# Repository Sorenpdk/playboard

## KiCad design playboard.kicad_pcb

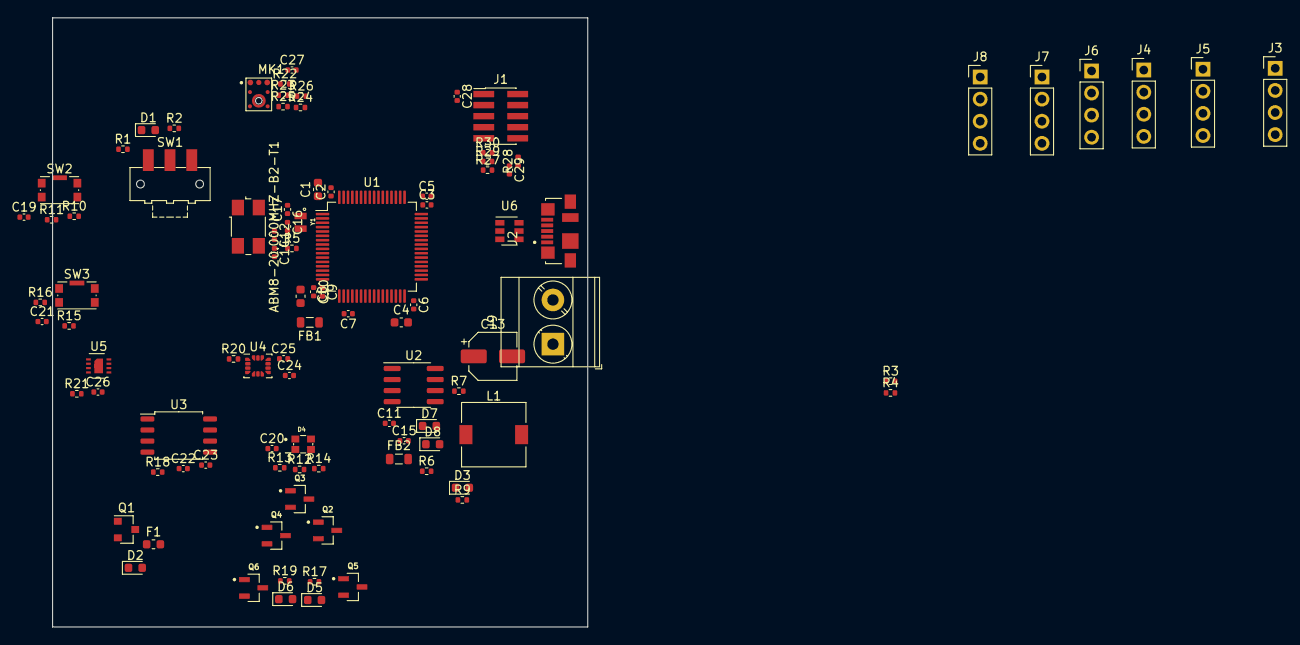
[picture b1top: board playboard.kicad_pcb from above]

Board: 2 copper layers, 61.5 x 70.0 mm, 96 parts (0 on the bottom side), 90 nets, no tracks yet.

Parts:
ABM8-20.000MHZ-B2-T1: 20MHz; Crystal_SMD_0603-4Pin_6.0x3.5mm
C1: 4u7; C_0603_1608Metric
C2, C3, C5, C6, C7, C9, C19, C21, C22, C23, C24, C25, C26, C27, C28, C29: 100n; C_0402_1005Metric
C4: 2u2; C_0603_1608Metric
C8: 1u; C_0603_1608Metric
C10: 10n; C_0402_1005Metric
C11: 47u; C_0402_1005Metric
C12, C14: 12p; C_0402_1005Metric
C13: 220u; CP_Elec_5x3
C15, C20: 10u; C_0402_1005Metric
C16, C17: 9pF; C_0402_1005Metric
D1: LED_Small; LED_0603_1608Metric
D2: B5817W-B5819W N1752; D_0603_1608Metric
D3, D5, D6: Blue; LED_0603_1608Metric
D4: ASMB-KTF0-0A306; LED_ASMB-KTF0-0A306
D7, D8: D_Schottky_Small; D_0603_1608Metric
F1: 500mA; Fuse_0603_1608Metric
FB1, FB2: 600 @ 600MHz; L_0805_2012Metric
J1: Conn_ARM_JTAG_SWD_10; PinHeader_2x05_P1.27mm_Vertical_SMD
J2: 47346-0001; MOLEX_47346-0001
J3, J4, J5, J6, J7, J8: Conn_01x04_Male; PinHeader_1x04_P2.54mm_Vertical
J9: Screw_Terminal_01x02; TerminalBlock_Phoenix_MKDS-3-2-5.08_1x02_P5.08mm_Horizontal
L1: 27u; L_7.3x7.3_H4.5
MK1: PMM-3738-VM1010-R; MIC_PMM-3738-VM1010-R
Q1: AO3401A; SOT-23
Q2, Q3, Q4, Q5, Q6: FDV305N; SOT95P240X111-3N
R1, R11, R16, R18, R20, R21, R24, R25: 10k; R_0402_1005Metric
R2, R9, R10, R15, R17, R19: 1k; R_0402_1005Metric
R3, R4: 2k2; R_0402_1005Metric
R5: 47; R_0402_1005Metric
R6: 3k; R_0402_1005Metric
R7: 1k78; R_0402_1005Metric
R12: 220; R_0402_1005Metric
R13, R14: 120; R_0402_1005Metric
R22: 0; R_0402_1005Metric
R23: 150k; R_0402_1005Metric
R26: 301k; R_0402_1005Metric
R27, R28, R29, R30: 22; R_0402_1005Metric
SW1: SW_SPDT; SW_SPDT_CK-JS102011SAQN
SW2, SW3: SW_Push; SW_Push_1P1T-SH_NO_CK_KMR2xxG
U1: STM32F411RETx; LQFP-64_10x10mm_P0.5mm
U2: MIC4684; SOIC-8_3.9x4.9mm_P1.27mm
U3: MX25R3235FM2xx1; SOP-8_5.28x5.23mm_P1.27mm
U4: LSM6DS3; LGA-14_3x2.5mm_P0.5mm_LayoutBorder3x4y
U5: SHT30-DIS; Sensirion_DFN-8-1EP_2.5x2.5mm_P0.5mm_EP1.1x1.7mm
U6: USBLC6-2SC6; SOT-23-6
Y1: ABS06-32.768KHZ-T; XTAL_ABS06-32.768KHZ-T

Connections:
+3.3VA: C8.1, C9.1, C10.1, FB1.2, U1.13
+3V3: C1.1, C2.1, C3.1, C5.1, C6.1, C7.1, C13.1, C22.1, C23.1, C24.2, C25.2, C26.2, C27.2, C28.1, D3.2, D5.2, D6.2, FB1.1, J1.1, J3.1, J5.1, J5.2, J7.1, L1.2, MK1.6, R3.2, R4.2, R6.2, R20.1, R21.1, SW1.1, U1.1, U1.19, U1.32, U1.48, U1.64, U3.8, U4.2, U4.3, U4.5, U4.8
ACC_CS!: R20.2, U1.24, U4.12
ACC_INT1: U1.27, U4.4
ACC_INT2: U1.28, U4.9
ACC_MISO_SA0: U1.22, U4.1
ACC_MOSI_SDA: U1.23, U4.14
ACC_SCLK_SCL: U1.21, U4.13
ADC1_IN1: J6.1, U1.15
BOOT0: R1.2, U1.60
BUTTON_1: C19.1, R10.1, R11.2, U1.26
BUTTON_2: C21.1, R15.1, R16.2, U1.25
DAC_OUT1: J6.4, U1.20
EXT_GPIO_PC0: J4.1, U1.8
EXT_GPIO_PC3: J3.2, U1.11
FLASH_CS!: U1.33, U3.1
FLASH_HOLD!: U1.40, U3.7
FLASH_MISO: R18.1, U1.35, U3.2
FLASH_MOSI: U1.36, U3.5
FLASH_SCLK: U1.34, U3.6
FLASH_WP!: U1.42, U3.3
GND: ABM8-20.000MHZ-B2-T1.2, ABM8-20.000MHZ-B2-T1.4, C1.2, C2.2, C3.2, C4.2, C5.2, C6.2, C7.2, C8.2, C9.2, C10.2, C11.2, C12.2, C13.2, C14.2, C16.2, C17.2, C19.2, C20.1, C21.2, C22.2, C23.2, C24.1, C25.1, C26.1, C27.1, C28.2, C29.2, D8.2, J1.3, J1.5, J1.9, J2.5, J5.3, J5.4, J6.2, J6.3, J9.1, MK1.4, MK1.8, Q1.1, Q2.3, Q3.3, Q4.3, Q5.3, Q6.3, R2.1, R7.1, R9.1, R18.2, R24.2, SW1.3, SW2.1, SW3.1, U1.12, U1.18, U1.31, U1.47, U1.63, U2.2, U2.6, U2.7, U3.4, U4.6, U4.7, U6.2
HSE_IN: ABM8-20.000MHZ-B2-T1.1, C12.1, U1.5
HSE_OUT: R5.2, U1.6
MCO_1: J8.2, U1.41
MIC_GA1: MK1.3, R22.1, R25.1
MIC_GA2: MK1.2, R23.2, R26.2
MIC_MODE: MK1.5, R24.1, U1.9
MIC_VOUT_ANALOG: MK1.1, U1.10
NRST: C29.1, R28.1, U1.7
unnamed: ABM8-20.000MHZ-B2-T1.3, C14.1, R5.1
unnamed: C4.1, U1.30
unnamed: C11.1, D7.2, FB2.2, U2.3, U2.8
unnamed: C15.1, D7.1, U2.4
unnamed: C15.2, D8.1, L1.1, U2.1
unnamed: D1.1, R2.2
unnamed: D1.2, R1.1, SW1.2
unnamed: D2.1, F1.2, Q1.2
unnamed: D3.1, R9.2
unnamed: D4.2, R12.1
unnamed: D4.3, R14.1
unnamed: D4.4, R13.1
unnamed: D5.1, R17.2
unnamed: D6.1, R19.2
unnamed: F1.1, FB2.1
unnamed: J1.2, R30.2
unnamed: J1.4, R29.2
unnamed: J1.6, R27.2
unnamed: J1.10, R28.2
unnamed: J2.S1, J2.S2, J2.S3, J2.S4, J2.S5, J2.S6
unnamed: Q2.2, R12.2
unnamed: Q3.2, R13.2
unnamed: Q4.2, R14.2
unnamed: Q5.2, R17.1
unnamed: Q6.2, R19.1
unnamed: R6.1, R7.2, U2.5
unnamed: R10.2, SW2.2
unnamed: R15.2, SW3.2
unnamed: R22.2, R23.1
unnamed: R25.2, R26.1
unnamed: U5.8, U5.9
OSC32_IN: C16.1, U1.3, Y1.1
OSC32_OUT: C17.1, U1.4, Y1.2
RGB_BLUE: Q4.1, U1.39
RGB_GREEN: Q3.1, U1.38
RGB_RED: Q2.1, U1.37
SPI3_MISO: J4.3, U1.52
SPI3_MOSI: J4.4, U1.53
SPI3_SCLK: J4.2, U1.51
SWCLK: R29.1, U1.49
SWDIO: R30.1, U1.46
SWO: R27.1, U1.55
TEMP_CS: R21.2, U1.56
TEMP_SCL: R4.1, U1.61
TEMP_SDA: R3.1, U1.59
TIM5_CH1: J3.4, U1.14
TIM11_CH1: J3.3, U1.62
USART1_RX: J8.4, U1.43
USART1_TX: J8.3, U1.58
USART2_RX: J7.3, U1.17
USART2_TX: J7.2, U1.16
USB_CONN_D+: J2.3, U6.1
USB_CONN_D-: J2.2, U6.3
USB_D+: U1.45, U6.6
USB_D-: U1.44, U6.4
USER_LD1: Q5.1, U1.29
USER_LD2: Q6.1, U1.50
VBUS: D2.2, J2.1, U6.5
VCC: C20.2, D4.1, J9.2, Q1.3, R11.1, R16.1
WOS_TRIGGER: MK1.7, U1.2

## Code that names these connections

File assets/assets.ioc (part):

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Mcu.Name=STM32F446R(C-E)Tx
Mcu.Package=LQFP64
Mcu.UserName=STM32F446RETx
PA0-WKUP.Signal=S_TIM5_CH1
PA1.Signal=ADCx_IN1
PA10.Signal=USART1_RX
PA11.Mode=Device_Only
PA11.Signal=USB_OTG_FS_DM
PA12.Mode=Device_Only
PA12.Signal=USB_OTG_FS_DP
PA13.Mode=Trace_Asynchronous_SW
PA13.Signal=SYS_JTMS-SWDIO
PA14.Mode=Trace_Asynchronous_SW
PA14.Signal=SYS_JTCK-SWCLK
PA15.GPIOParameters=GPIO_Label
PA15.GPIO_Label=USER_LED2
PA15.Signal=GPIO_Output
PA2.Mode=Asynchronous
PA2.Signal=USART2_TX
PA3.Mode=Asynchronous
PA3.Signal=USART2_RX
PA4.Signal=COMP_DAC1_group
PA5.GPIOParameters=GPIO_Label
PA5.GPIO_Label=ACC_SCLK_SCL
PA5.Mode=Full_Duplex_Master
PA5.Signal=SPI1_SCK
PA6.GPIOParameters=GPIO_Label
PA6.GPIO_Label=ACC_MISO_SA0
PA6.Mode=Full_Duplex_Master
PA6.Signal=SPI1_MISO
PA7.GPIOParameters=GPIO_Label
PA7.GPIO_Label=ACC_MOSI_SDA
PA7.Mode=Full_Duplex_Master
PA7.Signal=SPI1_MOSI
PA8.Mode=Clock-out-1
PA8.Signal=RCC_MCO_1
PA9.GPIOParameters=GPIO_Label
PA9.GPIO_Label=FLASH_WP\!
PA9.Signal=GPIO_Output
PB0.GPIOParameters=GPIO_Label
PB0.GPIO_Label=BUTTON_1
PB0.Signal=GPXTI0
PB1.GPIOParameters=GPIO_Label
PB1.GPIO_Label=ACC_INT1
PB1.Signal=GPXTI1
PB10.GPIOParameters=GPIO_Label
PB10.GPIO_Label=USER_LD1
PB10.Signal=GPIO_Output
PB12.GPIOParameters=GPIO_Label
PB12.GPIO_Label=FLASH_CS\!
PB12.Signal=GPIO_Output
PB13.GPIOParameters=GPIO_Label
PB13.GPIO_Label=FLASH_SCLK
PB13.Mode=Full_Duplex_Master
PB13.Signal=SPI2_SCK
PB14.GPIOParameters=GPIO_Label
PB14.GPIO_Label=FLASH_MISO
PB14.Mode=Full_Duplex_Master
PB14.Signal=SPI2_MISO
PB15.GPIOParameters=GPIO_Label
PB15.GPIO_Label=FLASH_MOSI
PB15.Mode=Full_Duplex_Master
PB15.Signal=SPI2_MOSI
PB2.GPIOParameters=GPIO_Label
PB2.GPIO_Label=ACC_INT2
PB2.Signal=GPXTI2
PB3.Mode=Trace_Asynchronous_SW
PB3.Signal=SYS_JTDO-SWO
PB4.GPIOParameters=GPIO_Label
PB4.GPIO_Label=TEMP_CS\!mn
PB4.Signal=GPIO_Output
PB5.GPIOParameters=GPIO_Label
PB5.GPIO_Label=TEMP_DATARDY
PB5.Signal=GPXTI5
PB6.Signal=USART1_TX
PB7.GPIOParameters=GPIO_Label
PB7.GPIO_Label=TEMP_SDA
PB7.Mode=I2C
PB7.Signal=I2C1_SDA
PB8.GPIOParameters=GPIO_Label
PB8.GPIO_Label=TEMP_SCL
PB8.Mode=I2C
PB8.Signal=I2C1_SCL
PB9.Signal=S_TIM11_CH1
PC0.GPIOParameters=GPIO_Label
PC0.GPIO_Label=EXT_GPIO_PC0
PC0.Signal=GPIO_Output
PC1.GPIOParameters=GPIO_Label
PC1.GPIO_Label=MIC_MODE
PC1.Signal=GPIO_Output
PC10.GPIOParameters=GPIO_Label
PC10.GPIO_Label=EXT_SPI_SCK
PC10.Mode=Full_Duplex_Master
PC10.Signal=SPI3_SCK
PC11.GPIOParameters=GPIO_Label
PC11.GPIO_Label=EXT_SPI_MISO
PC11.Mode=Full_Duplex_Master
PC11.Signal=SPI3_MISO
PC12.GPIOParameters=GPIO_Label
PC12.GPIO_Label=EXT_SPI_MOSI
PC12.Mode=Full_Duplex_Master
PC12.Signal=SPI3_MOSI
PC13.Mode=SYS_WakeUp1
PC13.Signal=SYS_WKUP1
PC14-OSC32_IN.Mode=LSE-External-Oscillator
PC14-OSC32_IN.Signal=RCC_OSC32_IN
PC15-OSC32_OUT.Mode=LSE-External-Oscillator
PC15-OSC32_OUT.Signal=RCC_OSC32_OUT
PC2.GPIOParameters=GPIO_Label
PC2.GPIO_Label=MIC_VOUT_ANALOG
PC2.Signal=ADCx_IN12
PC3.GPIOParameters=GPIO_Label
PC3.GPIO_Label=EXT_GPIO_PC3
PC3.Signal=GPIO_Output
PC4.GPIOParameters=GPIO_Label
PC4.GPIO_Label=ACC_CS\!
PC4.Signal=GPIO_Output
PC5.GPIOParameters=GPIO_Label
PC5.GPIO_Label=BUTTON_2
PC5.Signal=GPIO_Output
PC6.GPIOParameters=GPIO_Label
PC6.GPIO_Label=RGB_RED
PC6.Signal=S_TIM3_CH1
PC7.GPIOParameters=GPIO_Label
PC7.GPIO_Label=RGB_GREEN
PC7.Signal=S_TIM3_CH2
PC8.GPIOParameters=GPIO_Label
PC8.GPIO_Label=RGB_BLUE
PC8.Signal=S_TIM3_CH3
PC9.GPIOParameters=GPIO_Label
PC9.GPIO_Label=FLASH_HOLD\!
PC9.Signal=GPIO_Output
PD2.Signal=GPIO_Output
PH0-OSC_IN.Mode=HSE-External-Oscillator
PH0-OSC_IN.Signal=RCC_OSC_IN
PH1-OSC_OUT.Mode=HSE-External-Oscillator
PH1-OSC_OUT.Signal=RCC_OSC_OUT
board=custom
